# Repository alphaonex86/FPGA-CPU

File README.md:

# FPGA-CPU

An x86 CPU in an FPGA, on an interposer that plugs into an original PC CPU
socket and runs the board's stock BIOS, chipset, RAM and disks.

Planned brand name for the ASIC build: **LastUpgrade** — the last upgrade
for an old board: with its own memory (large L2, on-module RAM) and
SSE2, it should run a modern OS at correct performance.

Linked project: [FPGAmotherboard](https://github.com/alphaonex86/FPGAmotherboard),
the reverse (a real CPU on a board whose chipset is an FPGA) for the same
sockets; the socket KiCad models in `sockets/kicad/` come from it.

## Goals

- ISA: i686 + x87 + MMX + SSE + SSE2 first (modern software such as Node.js
  requires SSE2), then x86-64 and SSE3..SSE4.2 (x86-64-v2).
- Large on-chip L2 (>= 128 KB) to hide the slow front-side bus and board RAM.
- Best possible performance on each platform; many configurations (ISA level,
  cache sizes, clocks) from one RTL tree.
- Optional RAM on the module, next to the FPGA.
- Vendor-neutral RTL, so a popular model could later become an ASIC.

## Target boards

| Socket | Board | Chipset | Host bus |
|---|---|---|---|
| Socket 3 | Biostar MB-8433UUD | UMC 8881F / 8886BF | 486, 32-bit, 25/33/40 MHz |
| Socket 7 | Biostar MB-8500TTD | Intel 430TX | P5, 64-bit, 60/66 MHz |
| Socket 370 | VIA Apollo Pro 133A board (TBD) | VT82C694X | P6 AGTL+, 66/100/133 MHz |

## FPGAs

| FPGA | Logic | Block RAM | Package | Free toolchain |
|---|---|---|---|---|
| Altera Cyclone V E A9 — 5CEBA9/5CEFA9F23C8N (preferred) | 301k LE | 14.25 Mb | F484, 23x23 mm, 1.0 mm pitch, 224 I/O | Quartus Prime Lite (no licence) |
| Efinix Titanium Ti180 — TI180G400C3 | 176k LE | 13.1 Mb | 16x16 mm, 0.8 mm pitch, 274 I/O | Efinity (no licence) |

Both had authorized distributor stock at the end of 2026. The survey, I/O budget
per socket and power budget are in [FPGAlist/README.md](FPGAlist/README.md).

## Status

Planning: FPGAs chosen, documentation collected. No RTL yet.

## Layout

- `AGENTS.md` — project rules and requirements.
- `FPGAlist/` — FPGA survey; `CycloneV_A9/` and `Ti180_G400/` hold the vendor
  documentation, pin-outs, models, board references and toolchain notes.
- `sockets/` — per socket: CPU datasheets (bus protocol, pinout, power),
  chipset datasheets and the target board's manual, BIOS dump and photo;
  `kicad/` holds the socket footprints, symbols, 3D models and pin maps.
- `isa/` — x86 ISA manuals (Intel SDM, AMD APM, CPUID AP-485).
- `plan/` — interposer board plan (3 sockets x 2 FPGAs) and the prompt to run it.
- `fetch.sh` — downloads everything listed in the `sources.txt` files.

## Offline documentation

Vendor files are not stored in git (copyright, size). Download them with:

    ./fetch.sh FPGAlist/*/sources.txt sockets/sources.txt isa/sources.txt sockets/local-sources.txt

`sockets/local-sources.txt` copies files from the operator's local archive
(`file://`). No VT82C694X datasheet was found: use the VT82C694T one and
86Box's model (`FPGAcommon/86Box`).

Quartus and Efinity need a vendor account: see
[FPGAlist/CycloneV_A9/README.md](FPGAlist/CycloneV_A9/README.md) and
[FPGAlist/Ti180_G400/README.md](FPGAlist/Ti180_G400/README.md).

## License

GPL-3.0, see [LICENSE](LICENSE).

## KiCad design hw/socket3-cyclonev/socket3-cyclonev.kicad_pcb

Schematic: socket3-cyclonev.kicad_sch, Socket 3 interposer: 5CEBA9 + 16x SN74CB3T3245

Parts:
C1, C8, C12, C16: 10uF/25V; C_1210_3225Metric
C2: 4.7uF/25V; C_0805_2012Metric
C3, C4: 22uF/10V; C_1206_3216Metric
C5, C10, C14, C18, C21, C68, C69, C70, C90, C91, C92, C105, C106, C107, C108, C109, C110, C111, C112, C113, C114, C115, C116, C117, C118, C119, C120, C121: 100nF; C_0402_1005Metric
C6, C20, C44, C45, C46, C47, C48, C49, C50, C51: 10nF; C_0402_1005Metric
C7: 27nF; C_0402_1005Metric
C9, C13, C17: 22uF/6.3V; C_0805_2012Metric
C11, C15, C19: 3.3nF; C_0402_1005Metric
C22, C23, C24, C25, C26, C27, C28, C29, C30, C31, C32, C33, C34, C78, C79, C80, C81: 4.7nF; C_0402_P1.00
C35, C36, C37, C38, C39, C40, C41, C42, C43, C82, C83, C84, C85, C95: 10nF; C_0402_P1.00
C52, C53, C54, C55, C56, C57, C58, C59, C60, C61, C62, C63: 22nF; C_0402_1005Metric
C64, C65, C66, C67, C89: 47nF; C_0402_1005Metric
C71, C72: 220nF; C_0402_1005Metric
C73: 470nF; C_0402_1005Metric
C74, C93, C94: 1uF; C_0402_1005Metric
C75, C76, C77: 2.2nF; C_0402_P1.00
C86, C87: 22nF; C_0402_P1.00
C88: 47nF; C_0402_P1.00
C96, C98: 100nF; C_0402_P1.00
C97: 1uF; C_0402_P1.00
C99, C100, C101: 100uF/6.3V; C_1210_3225Metric
C102: 4.7uF; C_0603_1608Metric
C103: 10uF; C_0805_2012Metric
C104: 22uF; C_0805_2012Metric
F1: 2A; Fuse_1206_3216Metric
FB1: BLM18AG601SN1D; L_0603_1608Metric
J1: Conn_02x03_Odd_Even; PinHeader_2x03_P2.54mm_Vertical
J3: Barrel_Jack; BarrelJack_CUI_PJ-063AH_Horizontal
L1: 6.8uH FXL1040-6R8; L_Changjiang_FXL1040
L2, L3, L4: 2.2uH XFL4020-222; L_Coilcraft_XxL4020
PS1: TPS54620RHL; TI_RHL0014A
PS2, PS3, PS4: TPS62130RGT; VQFN-16-1EP_3x3mm_P0.5mm_EP1.68x1.68mm
R1, R2, R4: 4k7; R_0402_1005Metric
R3, R23, R26, R28, R29, R31, R33: 100k; R_0402_1005Metric
R5, R6, R7, R8, R9, R10, R11, R12, R13, R14, R15, R16, R17, R19, R20, R25, R36, R37: 10k; R_0402_1005Metric
R18: 1k; R_0402_1005Metric
R21: 2k0 1%; R_0402_1005Metric
R22: 1.33k; R_0402_1005Metric
R24: 52.3k; R_0402_1005Metric
R27: 37.4k; R_0402_1005Metric
R30: 215k; R_0402_1005Metric
R32: 316k; R_0402_1005Metric
R34: 68.1k 1%; R_0402_1005Metric
R35: 10k 1%; R_0402_1005Metric
TR01, TR02, TR03, TR04, TR05, TR06, TR07, TR08, TR09, TR10, TR11, TR12, TR13, TR14, TR15, TR16: SN74CB3T3245; TSSOP-20_4.4x6.5mm_P0.65mm
U1: FPGA_CycloneV_5CEFA9_F484; FPGA_CycloneV_5CEFA9_F484_BGA
U2: Socket3_Am5x86_PGA168; Socket3_Base_PGA168
U3: TLV6700DDC; SOT-23-6
U4: MT25QL01GBBB8ESF-0SIT; SOIC-16W_7.5x10.3mm_P1.27mm

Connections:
/A2: TR14.9 (A8), U1.N20
/A3: TR13.7 (A6), U1.N21
/A4: TR13.4 (A3), U1.W21
/A5: TR14.7 (A6), U1.W19
/A6: TR05.5 (A4), U1.Y21
/A7: TR14.8 (A7), U1.Y19
/A8: TR05.2 (A1), U1.AA22
/A9: TR14.6 (A5), U1.AB15
/A10: TR13.3 (A2), U1.Y20
/A11: TR13.6 (A5), U1.W22
/A12: TR06.2 (A1), U1.AB17
/A13: TR06.3 (A2), U1.AA18
/A14: TR14.5 (A4), U1.Y17
/A15: TR05.3 (A2), U1.Y22
/A16: TR06.4 (A3), U1.AA17
/A17: TR15.8 (A7), U1.Y15
/A18: TR05.4 (A3), U1.AB21
/A19: TR15.9 (A8), U1.AB11
/A20: TR06.5 (A4), U1.V20
/A20M#: TR11.3 (A2), U1.D13
/A21: TR06.8 (A7), U1.AB13
/A22: TR14.4 (A3), U1.AA15
/A23: TR14.3 (A2), U1.Y16
/A24: TR14.2 (A1), U1.AA14
/A25: TR05.6 (A5), U1.AB20
/A26: TR06.7 (A6), U1.V19
/A27: TR06.9 (A8), U1.AB12
/A28: TR05.8 (A7), U1.V21
/A29: TR15.4 (A3), U1.AA9
/A30: TR15.5 (A4), U1.AB8
/A31: TR15.6 (A5), U1.T19
/ADS#: TR13.5 (A4), U1.U22
/AHOLD: R5.1, TR01.4 (A3), U1.H21
/AS_DATA0: U1.AB4, U4.15 (DQ0)
/AS_DATA1: U1.AB3, U4.8 (DQ1)
/AS_DATA2: U1.AA5, U4.9 (DQ2)
/AS_DATA3: R17.1, U1.T4, U4.1 (DQ3)
/AS_DCLK: R16.1, U1.V3, U4.16 (C)
/AS_nCS: U1.R4, U4.7 (S#)
/BE0#: TR07.6 (A5), U1.AA10
/BE1#: TR07.8 (A7), U1.AB7
/BE2#: TR07.9 (A8), U1.AB6
/BE3#: TR11.6 (A5), U1.A7
/BLAST#: TR13.8 (A7), U1.M22
/BOFF#: TR03.9 (A8), U1.A10
/BRDY#: TR04.8 (A7), U1.K20
/BREQ: TR05.9 (A8), U1.AA19
/BS8#: TR03.7 (A6), U1.B10
/BS16#: TR02.9 (A8), U1.B17
/BUS_OE#: R36.1, TR01.19 (OE#), TR02.19 (OE#), TR03.19 (OE#), TR04.19 (OE#), TR05.19 (OE#), TR06.19 (OE#), TR07.19 (OE#), TR08.19 (OE#), TR09.19 (OE#), TR10.19 (OE#), TR11.19 (OE#), TR12.19 (OE#), TR13.19 (OE#), TR14.19 (OE#), TR15.19 (OE#), TR16.19 (OE#), U3.6 (OUTB)
/CACHE#: TR01.6 (A5), U1.B20
/CFG_CLKUSR: U1.T8
/CFG_CONF_DONE: R14.1, U1.K6
/CFG_CRC_ERROR: U1.T17
/CFG_CvP_CONFDONE: U1.R22
/CFG_DATA5: U1.U7
/CFG_DATA6: U1.R6
/CFG_DATA7: U1.U8
/CFG_DATA8: U1.R5
/CFG_DATA9: U1.W8
/CFG_DATA10: U1.P6
/CFG_DATA11: U1.W9
/CFG_DATA12: U1.N6
/CFG_DATA13: U1.U6
/CFG_DATA14: U1.T7
/CFG_DATA15: U1.V6
/CFG_DEV_CLRn: U1.P22
/CFG_DEV_OE: U1.R21
/CFG_INIT_DONE: U1.T18
/CFG_PR_DONE: U1.M6
/CFG_PR_ERROR: U1.M7
/CFG_PR_READY: U1.R7
/CFG_PR_REQUEST: U1.T20
/CFG_nCEO: U1.T22
/CFG_nCONFIG: R15.1, U1.A4
/CFG_nSTATUS: R13.1, U1.H5
/CLK: TR11.4 (A3), U1.H16
/CLKMUL: TR13.9 (A8), U1.AB22
/D0: TR15.3 (A2), U1.Y10
/D1: TR16.9 (A8), U1.AA7
/D2: TR16.8 (A7), U1.V13
/D3: TR12.5 (A4), U1.D6
/D4: TR08.2 (A1), U1.AB5
/D5: TR08.4 (A3), U1.M21
/D6: TR16.6 (A5), U1.V9
/D7: TR16.7 (A6), U1.V10
/D8: TR12.3 (A2), U1.B5
/D9: TR04.9 (A8), U1.B6
/D10: TR12.2 (A1), U1.D9
/D11: TR11.5 (A4), U1.A8
/D12: TR04.5 (A4), U1.E7
/D13: TR11.8 (A7), U1.B7
/D14: TR08.3 (A2), U1.Y9
/D15: TR04.7 (A6), U1.C6
/D16: TR16.5 (A4), U1.M20
/D17: TR03.2 (A1), U1.C8
/D18: TR03.5 (A4), U1.D12
/D19: TR09.9 (A8), U1.E19
/D20: TR03.6 (A5), U1.C11
/D21: TR09.7 (A6), U1.G21
/D22: TR03.8 (A7), U1.A9
/D23: TR02.2 (A1), U1.E14
/D24: TR02.5 (A4), U1.A13
/D25: TR09.5 (A4), U1.E21
/D26: TR10.9 (A8), U1.B12
/D27: TR11.2 (A1), U1.B11
/D28: TR10.7 (A6), U1.J19
/D29: TR10.3 (A2), U1.D17
/D30: TR10.6 (A5), U1.C15
/D31: TR01.5 (A4), U1.C20
/DP0: R9.1, TR15.2 (A1), U1.AA8
/DP1: R10.1, TR04.6 (A5), U1.D7
/DP2: R11.1, TR12.4 (A3), U1.E9
/DP3: R12.1, TR02.3 (A2), U1.A12
/D/C#: TR07.4 (A3), U1.AA12
/EADS#: TR01.9 (A8), U1.F22
/FERR#: TR02.6 (A5), U1.A14
/FLUSH#: TR02.7 (A6), U1.C16
/F_TCK: J1.1, R18.1, U1.V5
/F_TDI: J1.5, R20.1, U1.W5
/F_TDO: J1.6, U1.M5
/F_TMS: J1.3, R19.1, U1.P5
/GND: C1.2, C2.2, C3.2, C4.2, C6.2, C7.2, C8.2, C9.2, C10.2, C11.2, C12.2, C13.2, C14.2, C15.2, C16.2, C17.2, C18.2, C19.2, C20.2, C21.2, C22.2, C23.2, C24.2, C25.2, C26.2, C27.2, C28.2, C29.2, C30.2, C31.2, C32.2, C33.2, C34.2, C35.2, C36.2, C37.2, C38.2, C39.2, C40.2, C41.2, C42.2, C43.2, C44.2, C45.2, C46.2, C47.2, C48.2, C49.2, C50.2, C51.2, C52.2, C53.2, C54.2, C55.2, C56.2, C57.2, C58.2, C59.2, C60.2, C61.2, C62.2, C63.2, C64.2, C65.2, C66.2, C67.2, C68.2, C69.2, C70.2, C71.2, C72.2, C73.2, C74.2, C75.2, C76.2, C77.2, C78.2, C79.2, C80.2, C81.2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
/HITM#: TR09.8 (A7), U1.D19
/HLDA: TR06.6 (A5), U1.U21
/HOLD: R4.1, TR03.4 (A3), U1.C9
/IGNNE#: TR01.3 (A2), U1.J21
/INTR: TR09.6 (A5), U1.K22
/INV: TR02.8 (A7), U1.A15
/KEN#: TR11.7 (A6), U1.E12
/LOCK#: TR07.3 (A2), U1.Y14
/M/IO#: TR15.7 (A6), U1.AB10
/NC_A17: U1.A17
/NC_A18: U1.A18
/NC_A19: U1.A19
/NC_A20: U1.A20
/NC_A22: U1.A22
/NC_AA1: U1.AA1
/NC_AA2: U1.AA2
/NC_B3: U1.B3
/NC_B4: U1.B4
/NC_B22: U1.B22
/NC_C1: U1.C1
/NC_C2: U1.C2
/NC_C18: U1.C18
/NC_C19: U1.C19
/NC_D3: U1.D3
/NC_D4: U1.D4
/NC_D22: U1.D22
/NC_E1: U1.E1
/NC_E2: U1.E2
/NC_E10: U1.E10
/NC_E15: U1.E15
/NC_E16: U1.E16
/NC_E17: U1.E17
/NC_E20: U1.E20
/NC_E22: U1.E22
/NC_F7: U1.F7
/NC_F9: U1.F9
/NC_F10: U1.F10
/NC_F12: U1.F12
/NC_F13: U1.F13
/NC_F14: U1.F14
/NC_F15: U1.F15
/NC_F18: U1.F18
/NC_F19: U1.F19
/NC_F20: U1.F20
/NC_G1: U1.G1
/NC_G2: U1.G2
/NC_G6: U1.G6
/NC_G8: U1.G8
/NC_G10: U1.G10
/NC_G11: U1.G11
/NC_G12: U1.G12
/NC_G13: U1.G13
/NC_G15: U1.G15
/NC_G16: U1.G16
/NC_G17: U1.G17
/NC_G18: U1.G18
/NC_G20: U1.G20
/NC_H6: U1.H6
/NC_H8: U1.H8
/NC_H9: U1.H9
/NC_H10: U1.H10
/NC_H11: U1.H11
/NC_H13: U1.H13
/NC_H14: U1.H14
/NC_H15: U1.H15
/NC_H18: U1.H18
/NC_H20: U1.H20
/NC_J1: U1.J1
/NC_J2: U1.J2
/NC_J7: U1.J7
/NC_J8: U1.J8
/NC_J9: U1.J9
/NC_J11: U1.J11
/NC_J13: U1.J13
/NC_J17: U1.J17
/NC_J18: U1.J18
/NC_K7: U1.K7
/NC_K9: U1.K9
/NC_K16: U1.K16
/NC_K17: U1.K17
/NC_K19: U1.K19
/NC_L1: U1.L1
/NC_L2: U1.L2
/NC_L7: U1.L7
/NC_L8: U1.L8
/NC_L9: U1.L9
/NC_L17: U1.L17
/NC_L18: U1.L18
/NC_M8: U1.M8
/NC_M9: U1.M9
/NC_M16: U1.M16
/NC_M18: U1.M18
/NC_N1: U1.N1
/NC_N2: U1.N2
/NC_N8: U1.N8
/NC_N9: U1.N9
/NC_N16: U1.N16
/NC_N19: U1.N19
/NC_P7: U1.P7
/NC_P8: U1.P8
/NC_P9: U1.P9
/NC_P12: U1.P12
/NC_P14: U1.P14
/NC_P16: U1.P16
/NC_P17: U1.P17
/NC_P18: U1.P18
/NC_P19: U1.P19
/NC_PS1_10: PS1.10 (EN)
/NC_PS3_4: PS3.4 (PG)
/NC_PS4_4: PS4.4 (PG)
/NC_R1: U1.R1
/NC_R2: U1.R2
/NC_R9: U1.R9
/NC_R10: U1.R10
/NC_R11: U1.R11
/NC_R12: U1.R12
/NC_R14: U1.R14
/NC_R15: U1.R15
/NC_R16: U1.R16
/NC_R17: U1.R17
/NC_T9: U1.T9
/NC_T10: U1.T10
/NC_T12: U1.T12
/NC_T13: U1.T13
/NC_T14: U1.T14
/NC_T15: U1.T15
/NC_TR04_A1: TR04.2 (A1)
/NC_TR04_A2: TR04.3 (A2)
/NC_TR04_A3: TR04.4 (A3)
/NC_TR04_B1: TR04.18 (B1)
/NC_TR04_B2: TR04.17 (B2)
/NC_TR04_B3: TR04.16 (B3)
/NC_TR08_A4: TR08.5 (A4)
/NC_TR08_A5: TR08.6 (A5)
/NC_TR08_A6: TR08.7 (A6)
/NC_TR08_A7: TR08.8 (A7)
/NC_TR08_A8: TR08.9 (A8)
/NC_TR08_B4: TR08.15 (B4)
/NC_TR08_B5: TR08.14 (B5)
/NC_TR08_B6: TR08.13 (B6)
/NC_TR08_B7: TR08.12 (B7)
/NC_TR08_B8: TR08.11 (B8)
/NC_TR12_A5: TR12.6 (A5)
/NC_TR12_A6: TR12.7 (A6)
/NC_TR12_A7: TR12.8 (A7)
/NC_TR12_A8: TR12.9 (A8)
/NC_TR12_B5: TR12.14 (B5)
/NC_TR12_B6: TR12.13 (B6)
/NC_TR12_B7: TR12.12 (B7)
/NC_TR12_B8: TR12.11 (B8)
/NC_TR16_A1: TR16.2 (A1)
/NC_TR16_A2: TR16.3 (A2)
/NC_TR16_A3: TR16.4 (A3)
/NC_TR16_B1: TR16.18 (B1)
/NC_TR16_B2: TR16.17 (B2)
/NC_TR16_B3: TR16.16 (B3)
/NC_U1: U1.U1
/NC_U2: U1.U2
/NC_U2_A13: U2.A13 (InternalNC)
/NC_U2_C13: U2.C13 (InternalNC)
/NC_U2_J1: U2.J1 (InternalNC)
/NC_U4_4: U4.4 (DNU)
/NC_U4_5: U4.5 (DNU)
/NC_U4_6: U4.6 (DNU)
/NC_U4_11: U4.11 (DNU)
/NC_U4_12: U4.12 (DNU)
/NC_U4_13: U4.13 (DNU)
/NC_U4_14: U4.14 (DNU)
/NC_U10: U1.U10
/NC_U11: U1.U11
/NC_U12: U1.U12
/NC_U13: U1.U13
/NC_U15: U1.U15
/NC_U16: U1.U16
/NC_U17: U1.U17
/NC_V11: U1.V11
/NC_V14: U1.V14
/NC_V15: U1.V15
/NC_V16: U1.V16
/NC_V18: U1.V18
/NC_W1: U1.W1
/NC_W2: U1.W2
/NC_W16: U1.W16
/NC_Y3: U1.Y3
/NC_Y4: U1.Y4
/NC_Y6: U1.Y6
/NMI: TR01.7 (A6), U1.C21
/PCD: TR07.7 (A6), U1.Y11
/PCHK#: TR13.2 (A1), U1.AB18
/PG_1V1: PS2.4 (PG), PS3.13 (EN), PS4.13 (EN), R29.1
/PG_5V: PS1.14 (PWRGD), PS2.13 (EN), R26.1
/PLOCK#: TR05.7 (A6), U1.AA20
/PS1_BOOT: C5.1, PS1.13 (BOOT)
/PS1_COMP: PS1.8 (COMP), R22.1
/PS1_CZ: C7.1, R22.2
/PS1_FB: PS1.7 (VSENSE), R24.2, R25.1
/PS1_RT: PS1.1 (RT/CLK), R23.1
/PS1_SS: C6.1, PS1.9 (SS/TR)
/PS1_SW: C5.2, L1.1, PS1.11 (PH), PS1.12 (PH)
/PS2_FB: PS2.5 (FB), R27.2, R28.1
/PS2_SS: C11.1, PS2.9 (SS/TR)
/PS2_SW: L2.1, PS2.1 (SW), PS2.2 (SW), PS2.3 (SW)
/PS3_FB: PS3.5 (FB), R30.2, R31.1
/PS3_SS: C15.1, PS3.9 (SS/TR)
/PS3_SW: L3.1, PS3.1 (SW), PS3.2 (SW), PS3.3 (SW)
/PS4_FB: PS4.5 (FB), R32.2, R33.1
/PS4_SS: C19.1, PS4.9 (SS/TR)
/PS4_SW: L4.1, PS4.1 (SW), PS4.2 (SW), PS4.3 (SW)
/PWT: TR07.5 (A4), U1.U20
/RDY#: TR03.3 (A2), U1.L22
/RESET: TR10.2 (A1), U1.B16
/RREF_TL: R21.1, U1.A1
/SMI#: TR09.4 (A3), U1.D21
/SMIACT#: TR10.4 (A3), U1.B15
/SRESET: R6.1, TR02.4 (A3), U1.B13
/STPCLK#: TR11.9 (A8), U1.A5
/S_A2: TR14.11 (B8), U2.Q14 (A2)
/S_A3: TR13.13 (B6), U2.R15 (A3)
/S_A4: TR13.16 (B3), U2.S16 (A4)
/S_A5: TR14.13 (B6), U2.Q12 (A5)
/S_A6: TR05.15 (B4), U2.S15 (A6)
/S_A7: TR14.12 (B7), U2.Q13 (A7)
/S_A8: TR05.18 (B1), U2.R13 (A8)
/S_A9: TR14.14 (B5), U2.Q11 (A9)
/S_A10: TR13.17 (B2), U2.S13 (A10)
/S_A11: TR13.14 (B5), U2.R12 (A11)
/S_A12: TR06.18 (B1), U2.S7 (A12)
/S_A13: TR06.17 (B2), U2.Q10 (A13)
/S_A14: TR14.15 (B4), U2.S5 (A14)
/S_A15: TR05.17 (B2), U2.R7 (A15)
/S_A16: TR06.16 (B3), U2.Q9 (A16)
/S_A17: TR15.12 (B7), U2.Q3 (A17)
/S_A18: TR05.16 (B3), U2.R5 (A18)
/S_A19: TR15.11 (B8), U2.Q4 (A19)
/S_A20: TR06.15 (B4), U2.Q8 (A20)
/S_A20M#: TR11.17 (B2), U2.D15 (A20M)
/S_A21: TR06.12 (B7), U2.Q5 (A21)
/S_A22: TR14.16 (B3), U2.Q7 (A22)
/S_A23: TR14.17 (B2), U2.S3 (A23)
/S_A24: TR14.18 (B1), U2.Q6 (A24)
/S_A25: TR05.14 (B5), U2.R2 (A25)
/S_A26: TR06.13 (B6), U2.S2 (A26)
/S_A27: TR06.11 (B8), U2.S1 (A27)
/S_A28: TR05.12 (B7), U2.R1 (A28)
/S_A29: TR15.16 (B3), U2.P2 (A29)
/S_A30: TR15.15 (B4), U2.P3 (A30)
/S_A31: TR15.14 (B5), U2.Q1 (A31)
/S_ADS#: TR13.15 (B4), U2.S17 (ADS)
/S_AHOLD: TR01.16 (B3), U2.A17 (AHOLD)
/S_BE0#: TR07.14 (B5), U2.K15 (BE0)
/S_BE1#: TR07.12 (B7), U2.J16 (BE1)
/S_BE2#: TR07.11 (B8), U2.J15 (BE2)
/S_BE3#: TR11.14 (B5), U2.F17 (BE3)
/S_BLAST#: TR13.12 (B7), U2.R16 (BLAST)
/S_BOFF#: TR03.11 (B8), U2.D17 (BOFF)
/S_BRDY#: TR04.12 (B7), U2.H15 (BRDY)
/S_BREQ: R2.1, TR05.11 (B8), U2.Q15 (BREQ)
/S_BS8#: TR03.13 (B6), U2.D16 (BS8)
/S_BS16#: TR02.11 (B8), U2.C17 (BS16)
/S_CACHE#: TR01.14 (B5), U2.B12 (CACHE)
/S_CLK: TR11.16 (B3), U2.C3 (CLK)
/S_CLKMUL: TR13.11 (B8), U2.R17 (CLKMUL)
/S_D0: TR15.17 (B2), U2.P1 (D0)
/S_D1: TR16.11 (B8), U2.N2 (D1)
/S_D2: TR16.12 (B7), U2.N1 (D2)
/S_D3: TR12.15 (B4), U2.H2 (D3)
/S_D4: TR08.18 (B1), U2.M3 (D4)
/S_D5: TR08.16 (B3), U2.J2 (D5)
/S_D6: TR16.14 (B5), U2.L2 (D6)
/S_D7: TR16.13 (B6), U2.L3 (D7)
/S_D8: TR12.17 (B2), U2.F2 (D8)
/S_D9: TR04.11 (B8), U2.D1 (D9)
/S_D10: TR12.18 (B1), U2.E3 (D10)
/S_D11: TR11.15 (B4), U2.C1 (D11)
/S_D12: TR04.15 (B4), U2.G3 (D12)
/S_D13: TR11.12 (B7), U2.D2 (D13)
/S_D14: TR08.17 (B2), U2.K3 (D14)
/S_D15: TR04.13 (B6), U2.F3 (D15)
/S_D16: TR16.15 (B4), U2.J3 (D16)
/S_D17: TR03.18 (B1), U2.D3 (D17)
/S_D18: TR03.15 (B4), U2.C2 (D18)
/S_D19: TR09.11 (B8), U2.B1 (D19)
/S_D20: TR03.14 (B5), U2.A1 (D20)
/S_D21: TR09.13 (B6), U2.B2 (D21)
/S_D22: TR03.12 (B7), U2.A2 (D22)
/S_D23: TR02.18 (B1), U2.A4 (D23)
/S_D24: TR02.15 (B4), U2.A6 (D24)
/S_D25: TR09.15 (B4), U2.B6 (D25)
/S_D26: TR10.11 (B8), U2.C7 (D26)
/S_D27: TR11.18 (B1), U2.C6 (D27)
/S_D28: TR10.13 (B6), U2.C8 (D28)
/S_D29: TR10.17 (B2), U2.A8 (D29)
/S_D30: TR10.14 (B5), U2.C9 (D30)
/S_D31: TR01.15 (B4), U2.B8 (D31)
/S_DP0: TR15.18 (B1), U2.N3 (DP0)
/S_DP1: TR04.14 (B5), U2.F1 (DP1)
/S_DP2: TR12.16 (B3), U2.H3 (DP2)
/S_DP3: TR02.17 (B2), U2.A5 (DP3)
/S_D/C#: TR07.16 (B3), U2.M15 (D_C)
/S_EADS#: TR01.11 (B8), U2.B17 (EADS)
/S_FERR#: TR02.14 (B5), U2.C14 (FERR)
/S_FLUSH#: TR02.13 (B6), U2.C15 (FLUSH)
/S_HITM#: TR09.12 (B7), U2.A12 (HITM)
/S_HLDA: R1.1, TR06.14 (B5), U2.P15 (HLDA)
/S_HOLD: TR03.16 (B3), U2.E15 (HOLD)
/S_IGNNE#: TR01.17 (B2), U2.A15 (IGNNE)
/S_INTR: TR09.14 (B5), U2.A16 (INTR)
/S_INV: TR02.12 (B7), U2.A10 (INV)
/S_KEN#: TR11.13 (B6), U2.F15 (KEN)
/S_LOCK#: TR07.17 (B2), U2.N15 (LOCK)
/S_M/IO#: TR15.13 (B6), U2.N16 (M_IO)
/S_NMI: TR01.13 (B6), U2.B15 (NMI)
/S_PCD: TR07.13 (B6), U2.J17 (PCD)
/S_PCHK#: TR13.18 (B1), U2.Q17 (PCHK)
/S_PLOCK#: TR05.13 (B6), U2.Q16 (PLOCK)
/S_PWT: TR07.15 (B4), U2.L15 (PWT)
/S_RDY#: TR03.17 (B2), U2.F16 (RDY)
/S_RESET: R3.1, TR10.18 (B1), U2.C16 (RESET)
/S_SMI#: TR09.16 (B3), U2.B10 (SMI)
/S_SMIACT#: TR10.16 (B3), U2.C12 (SMIACT)
/S_SRESET: TR02.16 (B3), U2.C10 (SRESET)
/S_STPCLK#: TR11.11 (B8), U2.G15 (STPCLK)
/S_TCK: TR10.12 (B7), U2.A3 (TCK)
/S_TDI: TR01.18 (B1), U2.A14 (TDI)
/S_TDO: TR01.12 (B7), U2.B16 (TDO)
/S_TMS: TR09.18 (B1), U2.B14 (TMS)
/S_UP#: TR10.15 (B4), U2.C11 (UP)
/S_VCC: R34.1, U2.B7 (VCC), U2.B9 (VCC), U2.B11 (VCC), U2.C4 (VCC), U2.C5 (VCC), U2.E2 (VCC), U2.E16 (VCC), U2.G2 (VCC), U2.G16 (VCC), U2.H16 (VCC), U2.K2 (VCC), U2.K16 (VCC), U2.L16 (VCC), U2.M2 (VCC), U2.M16 (VCC), U2.P16 (VCC), U2.R3 (VCC), U2.R6 (VCC), U2.R8 (VCC), U2.R9 (VCC), U2.R10 (VCC), U2.R11 (VCC), U2.R14 (VCC)
/S_WB/WT#: TR09.17 (B2), U2.B13 (WB_WT)
/S_W/R#: TR07.18 (B1), U2.N17 (W_R)
/TCK: TR10.8 (A7), U1.C13
/TDI: TR01.2 (A1), U1.B18
/TDO: TR01.8 (A7), U1.J22
/TMS: TR09.2 (A1), U1.G22
/UP#: R8.1, TR10.5 (A4), U1.K21
/V3V3: C17.1, C75.1, C76.1, C77.1, C78.1, C79.1, C80.1, C81.1, C82.1, C83.1, C84.1, C85.1, C86.1, C87.1, C88.1, C89.1, C90.1, C91.1, C92.1, C93.1, C94.1, C103.1, C104.1, C105.1, C106.1, C107.1, C108.1, C109.1, C110.1, C111.1, C112.1, C113.1, C114.1, C115.1, C116.1, C117.1, C118.1, C119.1, C120.1, C121.1, L4.2, PS4.14 (VOS), R8.2, R9.2, R10.2, R11.2, R12.2, R13.2, R14.2, R15.2, R17.2, R19.2, R20.2, R32.1, R36.2, R37.2, TR01.20 (VCC), TR02.20 (VCC), TR03.20 (VCC), TR04.20 (VCC), TR05.20 (VCC), TR06.20 (VCC), TR07.20 (VCC), TR08.20 (VCC), TR09.20 (VCC), TR10.20 (VCC), TR11.20 (VCC), TR12.20 (VCC), TR13.20 (VCC), TR14.20 (VCC), TR15.20 (VCC), TR16.20 (VCC), U1.A6, U1.A16, U1.AA16, U1.AA21, U1.B19, U1.C7, U1.C10, U1.C12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
/V5: C3.1, C4.1, C8.1, C10.1, C12.1, C14.1, C16.1, C18.1, C21.1, L1.2, PS2.10 (AVIN), PS2.11 (PVIN), PS2.12 (PVIN), PS3.10 (AVIN), PS3.11 (PVIN), PS3.12 (PVIN), PS4.10 (AVIN), PS4.11 (PVIN), PS4.12 (PVIN), R24.1, R26.2, R29.2, U3.5 (VDD)
/V12: C1.1, C2.1, F1.2, PS1.4 (PVIN), PS1.5 (PVIN), PS1.6 (VIN)
/V12_IN: F1.1, J3.1
/VCCA_FPLL25: C98.1, FB1.2, U1.F4, U1.H19, U1.M3, U1.T3, U1.T5, U1.U18
/VCC_1V1: C9.1, C22.1, C23.1, C24.1, C25.1, C26.1, C27.1, C28.1, C29.1, C30.1, C31.1, C32.1, C33.1, C34.1, C35.1, C36.1, C37.1, C38.1, C39.1, C40.1, C41.1, C42.1, C43.1, C44.1, C45.1, C46.1, C47.1, C48.1, C49.1, C50.1, C51.1, C52.1, C53.1, C54.1, C55.1, C56.1, C57.1, C58.1, C59.1, C60.1, C61.1, C62.1, C63.1, C64.1, C65.1, C66.1, C67.1, C68.1, C69.1, C70.1, C71.1, C72.1, C73.1, C74.1, C99.1, C100.1, C101.1, C102.1, L2.2, PS2.14 (VOS), R27.1, U1.J4, U1.J10, U1.J12, U1.J14, U1.J16, U1.K3, U1.K5, U1.K11, U1.K13, U1.K15, U1.L4, U1.L10, U1.L12, U1.L14, U1.L16, U1.M11, U1.M13, U1.M15, U1.N4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
/VCC_AUX25: C13.1, C95.1, C96.1, C97.1, FB1.1, L3.2, PS3.14 (VOS), R30.1, U1.A3, U1.D11, U1.D18, U1.E6, U1.W7, U1.W13, U1.W18
/VCORE_OK: R37.1, U1.L19, U3.1 (OUTA)
/VCORE_SENSE: C20.1, R34.2, R35.1, U3.3 (INA+), U3.4 (INB-)
/WB/WT#: R7.1, TR09.3 (A2), U1.B21
/W/R#: TR07.2 (A1), U1.AA13

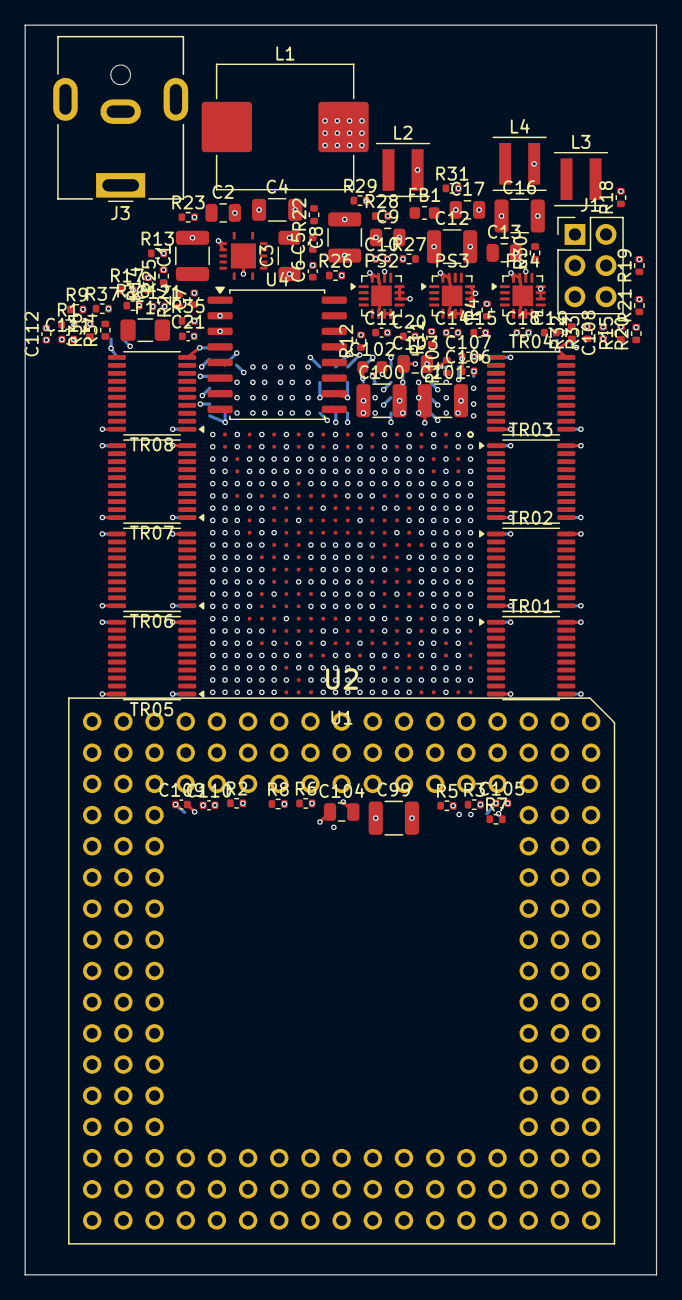
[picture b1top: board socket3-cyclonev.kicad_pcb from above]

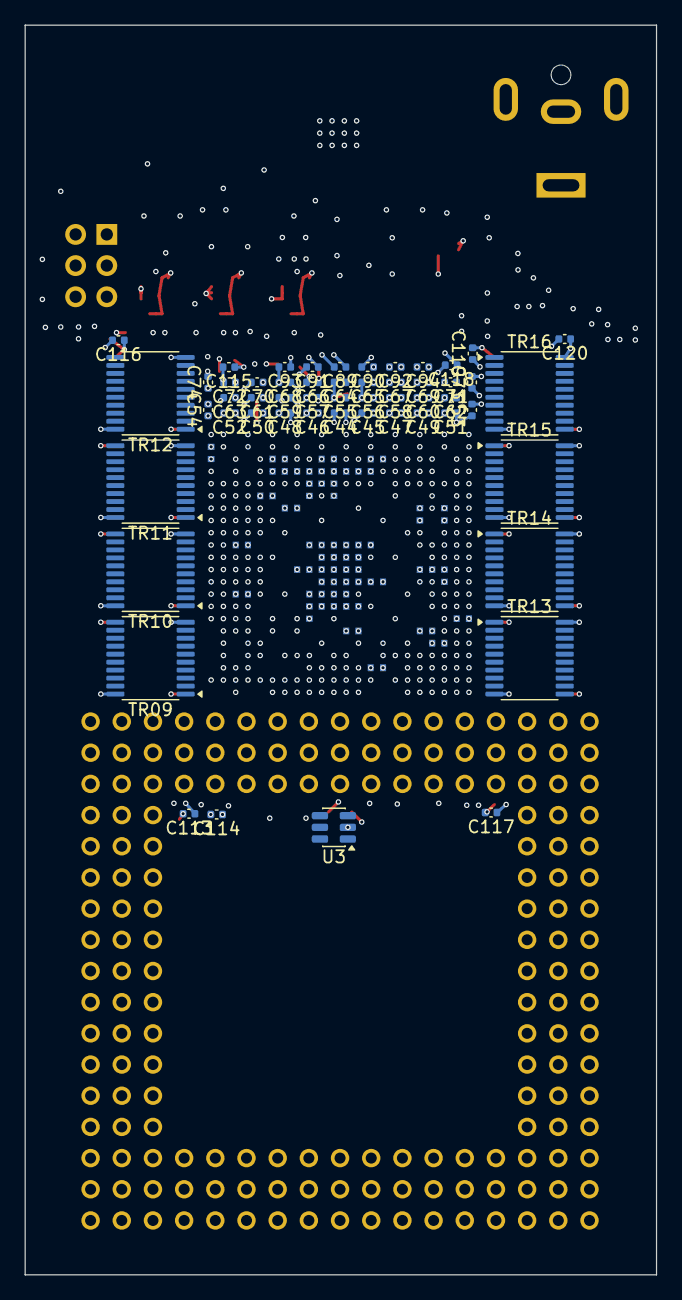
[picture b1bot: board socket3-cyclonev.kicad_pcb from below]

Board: 8 copper layers, 51.4 x 101.8 mm, 190 parts (94 on the bottom side), 270 nets.

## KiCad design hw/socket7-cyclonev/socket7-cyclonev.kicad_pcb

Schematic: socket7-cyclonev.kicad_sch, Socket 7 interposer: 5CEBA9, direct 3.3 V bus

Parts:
C1: 22uF/10V; C_0805_2012Metric
C2, C53, C54, C55, C75, C76, C77, C88: 100nF; C_0402_1005Metric
C3, C84: 22uF/6.3V; C_0805_2012Metric
C4: 1nF; C_0402_1005Metric
C5: 10uF/10V; C_0805_2012Metric
C6, C59, C78, C79: 1uF; C_0402_1005Metric
C7, C8, C9, C10, C11, C12, C13, C14, C15, C16, C17, C18, C19, C63, C64, C65, C66: 4.7nF; C_0402_P1.00
C20, C21, C22, C23, C24, C25, C26, C27, C28, C67, C68, C69, C70, C80: 10nF; C_0402_P1.00
C29, C30, C31, C32, C33, C34, C35, C36: 10nF; C_0402_1005Metric
C37, C38, C39, C40, C41, C42, C43, C44, C45, C46, C47, C48: 22nF; C_0402_1005Metric
C49, C50, C51, C52, C74: 47nF; C_0402_1005Metric
C56, C57: 220nF; C_0402_1005Metric
C58: 470nF; C_0402_1005Metric
C60, C61, C62: 2.2nF; C_0402_P1.00
C71, C72: 22nF; C_0402_P1.00
C73: 47nF; C_0402_P1.00
C81, C83: 100nF; C_0402_P1.00
C82: 1uF; C_0402_P1.00
C85: 10uF; C_0805_2012Metric
C86: 22uF; C_0805_2012Metric
C87: 4.7uF; C_0603_1608Metric
FB1: BLM18AG601SN1D; L_0603_1608Metric
J1: Conn_02x03_Odd_Even; PinHeader_2x03_P2.54mm_Vertical
L1: 1uH XFL4020-102; L_Coilcraft_XxL4020
PS1: TLV62585PDRL; SOT-563
PS2: TLV75725PDBVR; SOT-23-5
R1, R2, R3, R4, R5, R6, R7: 4k7; R_0402_1005Metric
R8, R9, R10, R11, R12, R14, R15: 10k; R_0402_1005Metric
R13: 1k; R_0402_1005Metric
R16: 2k0 1%; R_0402_1005Metric
R17: 82.5k; R_0402_1005Metric
R18, R19: 100k; R_0402_1005Metric
U1: FPGA_CycloneV_5CEFA9_F484; FPGA_CycloneV_5CEFA9_F484_BGA
U2: Intel_Pentium_MMX_P55C_Socket7; Socket7_Base_PGA296
U3: TPS22918DBVR; SOT-23-6
U4: MT25QL01GBBB8ESF-0SIT; SOIC-16W_7.5x10.3mm_P1.27mm

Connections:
/A3: U1.B7, U2.AL35 (A3)
/A4: U1.A7, U2.AM34 (A4)
/A5: U1.C9, U2.AK32 (A5)
/A6: U1.C11, U2.AN33 (A6)
/A7: U1.E12, U2.AL33 (A7)
/A8: U1.D12, U2.AM32 (A8)
/A9: U1.F14, U2.AK30 (A9)
/A10: U1.A10, U2.AN31 (A10)
/A11: U1.A8, U2.AL31 (A11)
/A12: U1.A9, U2.AL29 (A12)
/A13: U1.B10, U2.AK28 (A13)
/A14: U1.B11, U2.AL27 (A14)
/A15: U1.D13, U2.AK26 (A15)
/A16: U1.E14, U2.AL25 (A16)
/A17: U1.B12, U2.AK24 (A17)
/A18: U1.C13, U2.AL23 (A18)
/A19: U1.A12, U2.AK22 (A19)
/A20: U1.B13, U2.AL21 (A20)
/A20M#: U1.E16, U2.AK08 (A20M#)
/A21: U1.E9, U2.AF34 (A21)
/A22: U1.C6, U2.AH36 (A22)
/A23: U1.D6, U2.AE33 (A23)
/A24: U1.D7, U2.AG35 (A24)
/A25: U1.D9, U2.AJ35 (A25)
/A26: U1.B5, U2.AH34 (A26)
/A27: R7.1, U1.F12, U2.AG33 (A27)
/A28: U1.B6, U2.AK36 (A28)
/A29: U1.A5, U2.AK34 (A29)
/A30: U1.F13, U2.AM36 (A30)
/A31: U1.C8, U2.AJ33 (A31)
/ADS#: U1.C20, U2.AJ05 (ADS#)
/ADSC#: U1.C21, U2.AM02 (ADSC#)
/AHOLD: U1.K22, U2.V04 (AHOLD)
/AP: U1.D21, U2.AK02 (AP)
/APCHK#: U1.F22, U2.AE05 (APCHK#)
/AS_DATA0: U1.AB4, U4.15 (DQ0)
/AS_DATA1: U1.AB3, U4.8 (DQ1)
/AS_DATA2: U1.AA5, U4.9 (DQ2)
/AS_DATA3: R12.1, U1.T4, U4.1 (DQ3)
/AS_DCLK: R11.1, U1.V3, U4.16 (C)
/AS_nCS: U1.R4, U4.7 (S#)
/BE0#: U1.F15, U2.AL09 (BE0#)
/BE1#: U1.B17, U2.AK10 (BE1#)
/BE2#: U1.C16, U2.AL11 (BE2#)
/BE3#: U1.E15, U2.AK12 (BE3#)
/BE4#: U1.B16, U2.AL13 (BE4#)
/BE5#: U1.C15, U2.AK14 (BE5#)
/BE6#: U1.B15, U2.AL15 (BE6#)
/BE7#: U1.A15, U2.AK16 (BE7#)
/BOFF#: U1.J19, U2.Z04 (BOFF#)
/BP2: R5.1, U1.M22, U2.S03 (BP2)
/BP3: R6.1, U1.M21, U2.S05 (BP3)
/BRDY#: U1.K19, U2.X04 (BRDY#)
/BRDYC#: U1.J22, U2.Y03 (BRDYC#)
/BREQ: R1.1, U1.J17, U2.AJ01 (BREQ)
/BUSCHK#: U1.D17, U2.AL07 (BUSCHK#)
/CACHE#: U1.L22, U2.U03 (CACHE#)
/CFG_CLKUSR: U1.T8
/CFG_CONF_DONE: R9.1, U1.K6
/CFG_CRC_ERROR: U1.T17
/CFG_CvP_CONFDONE: U1.R22
/CFG_DATA5: U1.U7
/CFG_DATA6: U1.R6
/CFG_DATA7: U1.U8
/CFG_DATA8: U1.R5
/CFG_DATA9: U1.W8
/CFG_DATA10: U1.P6
/CFG_DATA11: U1.W9
/CFG_DATA12: U1.N6
/CFG_DATA13: U1.U6
/CFG_DATA14: U1.T7
/CFG_DATA15: U1.V6
/CFG_DEV_CLRn: U1.P22
/CFG_DEV_OE: U1.R21
/CFG_INIT_DONE: U1.T18
/CFG_PR_DONE: U1.M6
/CFG_PR_ERROR: U1.M7
/CFG_PR_READY: U1.R7
/CFG_PR_REQUEST: U1.T20
/CFG_nCEO: U1.T22
/CFG_nCONFIG: R10.1, U1.A4
/CFG_nSTATUS: R8.1, U1.H5
/CLK: U1.W16, U2.AK18 (CLK)
/CPUTYP: U1.L7, U2.Q35 (CPUTYP)
/D0: U1.T9, U2.K34 (D0)
/D1: U1.U10, U2.G35 (D1)
/D2: U1.T10, U2.J35 (D2)
/D3: U1.V9, U2.G33 (D3)
/D4: U1.T12, U2.F36 (D4)
/D5: U1.U11, U2.F34 (D5)
/D6: U1.T13, U2.E35 (D6)
/D7: U1.T14, U2.E33 (D7)
/D8: U1.AB5, U2.D34 (D8)
/D9: U1.U12, U2.C37 (D9)
/D10: U1.AA7, U2.C35 (D10)
/D11: U1.AB6, U2.B36 (D11)
/D12: U1.Y9, U2.D32 (D12)
/D13: U1.AA8, U2.B34 (D13)
/D14: U1.U13, U2.C33 (D14)
/D15: U1.AB7, U2.A35 (D15)
/D16: U1.AB8, U2.B32 (D16)
/D17: U1.AA9, U2.C31 (D17)
/D18: U1.T15, U2.A33 (D18)
/D19: U1.V13, U2.D28 (D19)
/D20: U1.AA10, U2.B30 (D20)
/D21: U1.Y11, U2.C29 (D21)
/D22: U1.AB10, U2.A31 (D22)
/D23: U1.AB11, U2.D26 (D23)
/D24: U1.U15, U2.C27 (D24)
/D25: U1.AA13, U2.C23 (D25)
/D26: U1.AB12, U2.D24 (D26)
/D27: U1.AB13, U2.C21 (D27)
/D28: U1.Y14, U2.D22 (D28)
/D29: U1.Y15, U2.C19 (D29)
/D30: U1.AA14, U2.D20 (D30)
/D31: U1.AB15, U2.C17 (D31)
/D32: U1.Y16, U2.C15 (D32)
/D33: U1.U16, U2.D16 (D33)
/D34: U1.AA17, U2.C13 (D34)
/D35: U1.AB17, U2.D14 (D35)
/D36: U1.AB18, U2.C11 (D36)
/D37: U1.Y17, U2.D12 (D37)
/D38: U1.AA19, U2.C09 (D38)
/D39: U1.AA18, U2.D10 (D39)
/D40: U1.U17, U2.D08 (D40)
/D41: U1.AA20, U2.A05 (D41)
/D42: U1.AB20, U2.E09 (D42)
/D43: U1.Y20, U2.B04 (D43)
/D44: U1.V18, U2.D06 (D44)
/D45: U1.W19, U2.C05 (D45)
/D46: U1.AB21, U2.E07 (D46)
/D47: U1.AA22, U2.C03 (D47)
/D48: U1.Y21, U2.D04 (D48)
/D49: U1.V19, U2.E05 (D49)
/D50: U1.R16, U2.D02 (D50)
/D51: U1.W21, U2.F04 (D51)
/D52: U1.Y22, U2.E03 (D52)
/D53: U1.V20, U2.G05 (D53)
/D54: U1.R17, U2.E01 (D54)
/D55: U1.V21, U2.G03 (D55)
/D56: U1.U20, U2.H04 (D56)
/D57: U1.U21, U2.J03 (D57)
/D58: U1.T19, U2.J05 (D58)
/D59: U1.P17, U2.K04 (D59)
/D60: U1.U22, U2.L05 (D60)
/D61: U1.P18, U2.L03 (D61)
/D62: U1.P19, U2.M04 (D62)
/D63: U1.N20, U2.N03 (D63)
/DP0: U1.V10, U2.D36 (DP0)
/DP1: U1.Y10, U2.D30 (DP1)
/DP2: U1.AA12, U2.C25 (DP2)
/DP3: U1.AA15, U2.D18 (DP3)
/DP4: U1.Y19, U2.C07 (DP4)
/DP5: U1.AB22, U2.F06 (DP5)
/DP6: U1.W22, U2.F02 (DP6)
/DP7: U1.N19, U2.N05 (DP7)
/D/C#: U1.B21, U2.AK04 (D/C#)
/EADS#: U1.D19, U2.AM04 (EADS#)
/EWBE#: U1.K21, U2.W03 (EWBE#)
/FERR#: U1.N21, U2.Q05 (FERR#)
/FLUSH#: U1.B18, U2.AN07 (FLUSH#)
/F_TCK: J1.1, R13.1, U1.V5
/F_TDI: J1.5, R15.1, U1.W5
/F_TDO: J1.6, U1.M5
/F_TMS: J1.3, R14.1, U1.P5
/GND: C1.2, C2.2, C3.2, C4.2, C5.2, C6.2, C7.2, C8.2, C9.2, C10.2, C11.2, C12.2, C13.2, C14.2, C15.2, C16.2, C17.2, C18.2, C19.2, C20.2, C21.2, C22.2, C23.2, C24.2, C25.2, C26.2, C27.2, C28.2, C29.2, C30.2, C31.2, C32.2, C33.2, C34.2, C35.2, C36.2, C37.2, C38.2, C39.2, C40.2, C41.2, C42.2, C43.2, C44.2, C45.2, C46.2, C47.2, C48.2, C49.2, C50.2, C51.2, C52.2, C53.2, C54.2, C55.2, C56.2, C57.2, C58.2, C59.2, C60.2, C61.2, C62.2, C63.2, C64.2, C65.2, C66.2, C67.2, C68.2, C69.2, C70.2, C71.2, C72.2, C73.2, C74.2, C75.2, C76.2, C77.2, C78.2, C79.2, C80.2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
/HIT#: U1.B20, U2.AK06 (HIT#)
/HITM#: U1.G16, U2.AL05 (HITM#)
/HLDA: U1.E21, U2.AJ03 (HLDA)
/HOLD: U1.G22, U2.AB04 (HOLD)
/IERR#: U1.M18, U2.P04 (IERR#)
/IGNNE#: U1.G8, U2.AA35 (IGNNE#)
/INIT: U1.G11, U2.AA33 (INIT)
/INTR/LINT0: U1.E7, U2.AD34 (INTR/LINT0)
/INV: U1.L19, U2.U05 (INV)
/KEN#: U1.K20, U2.W05 (KEN#)
/LOCK#: U1.G18, U2.AH04 (LOCK#)
/M/IO#: U1.L18, U2.T04 (M/IO#)
/NA#: U1.J21, U2.Y05 (NA#)
/NC_A17: U1.A17
/NC_A18: U1.A18
/NC_A19: U1.A19
/NC_A20: U1.A20
/NC_A22: U1.A22
/NC_AA1: U1.AA1
/NC_AA2: U1.AA2
/NC_B3: U1.B3
/NC_B4: U1.B4
/NC_B22: U1.B22
/NC_C1: U1.C1
/NC_C2: U1.C2
/NC_C18: U1.C18
/NC_C19: U1.C19
/NC_D3: U1.D3
/NC_D4: U1.D4
/NC_D22: U1.D22
/NC_E1: U1.E1
/NC_E2: U1.E2
/NC_E10: U1.E10
/NC_E17: U1.E17
/NC_E20: U1.E20
/NC_E22: U1.E22
/NC_F9: U1.F9
/NC_F10: U1.F10
/NC_F18: U1.F18
/NC_F19: U1.F19
/NC_F20: U1.F20
/NC_G1: U1.G1
/NC_G2: U1.G2
/NC_G10: U1.G10
/NC_G13: U1.G13
/NC_G20: U1.G20
/NC_H8: U1.H8
/NC_H9: U1.H9
/NC_H10: U1.H10
/NC_H11: U1.H11
/NC_H13: U1.H13
/NC_H14: U1.H14
/NC_H15: U1.H15
/NC_H16: U1.H16
/NC_H20: U1.H20
/NC_J1: U1.J1
/NC_J2: U1.J2
/NC_J8: U1.J8
/NC_J9: U1.J9
/NC_J11: U1.J11
/NC_J13: U1.J13
/NC_K9: U1.K9
/NC_K16: U1.K16
/NC_L1: U1.L1
/NC_L2: U1.L2
/NC_L9: U1.L9
/NC_M8: U1.M8
/NC_M9: U1.M9
/NC_M16: U1.M16
/NC_N1: U1.N1
/NC_N2: U1.N2
/NC_N9: U1.N9
/NC_N16: U1.N16
/NC_P9: U1.P9
/NC_P12: U1.P12
/NC_P14: U1.P14
/NC_P16: U1.P16
/NC_PS2_4: PS2.4 (NC)
/NC_R1: U1.R1
/NC_R2: U1.R2
/NC_R10: U1.R10
/NC_R11: U1.R11
/NC_R12: U1.R12
/NC_R14: U1.R14
/NC_R15: U1.R15
/NC_U1: U1.U1
/NC_U2: U1.U2
/NC_U4_4: U4.4 (DNU)
/NC_U4_5: U4.5 (DNU)
/NC_U4_6: U4.6 (DNU)
/NC_U4_11: U4.11 (DNU)
/NC_U4_12: U4.12 (DNU)
/NC_U4_13: U4.13 (DNU)
/NC_U4_14: U4.14 (DNU)
/NC_V11: U1.V11
/NC_V14: U1.V14
/NC_V15: U1.V15
/NC_V16: U1.V16
/NC_W1: U1.W1
/NC_W2: U1.W2
/NC_Y3: U1.Y3
/NC_Y4: U1.Y4
/NC_Y6: U1.Y6
/NMI/LINT1: U1.G12, U2.AC33 (NMI/LINT1)
/PCD: U1.H18, U2.AG05 (PCD)
/PCHK#: U1.K17, U2.AF04 (PCHK#)
/PEN#: U1.G6, U2.Z34 (PEN#)
/PG_1V1: PS1.6 (PG), PS2.3 (EN), R19.1, U3.3 (ON)
/PM0/BP0: R3.1, U1.L17, U2.Q03 (PM0/BP0)
/PM1/BP1: R4.1, U1.M20, U2.R04 (PM1/BP1)
/PRDY: U1.G21, U2.AC05 (PRDY)
/PS1_FB: PS1.5 (FB), R17.2, R18.1
/PS1_SW: L1.1, PS1.2 (SW)
/PWT: U1.E19, U2.AL03 (PWT)
/RESET: U1.A13, U2.AK20 (RESET)
/RREF_TL: R16.1, U1.A1
/SCYC: R2.1, U1.A14, U2.AL17 (SCYC)
/SMI#: U1.F7, U2.AB34 (SMI#)
/SMIACT#: U1.J18, U2.AG03 (SMIACT#)
/STPCLK#: U1.K7, U2.V34 (STPCLK#)
/S_VCC2: C1.1, C2.1, PS1.3 (VIN), PS1.4 (EN), U2.A07 (VCC2), U2.A09 (VCC2), U2.A11 (VCC2), U2.A13 (VCC2), U2.A15 (VCC2), U2.A17 (VCC2), U2.AA01 (VCC2), U2.AC01 (VCC2), U2.AE01 (VCC2), U2.AG01 (VCC2), U2.AN09 (VCC2), U2.AN11 (VCC2), U2.AN13 (VCC2), U2.AN15 (VCC2), U2.AN17 (VCC2), U2.AN19 (VCC2), U2.G01 (VCC2), U2.J01 (VCC2), U2.L01 (VCC2), U2.N01 (VCC2), U2.Q01 (VCC2), U2.S01 (VCC2), U2.U01 (VCC2), U2.W01 (VCC2), U2.Y01 (VCC2)
/S_VCC3: C5.1, C6.1, PS2.1 (IN), U2.A19 (VCC3), U2.A21 (VCC3), U2.A23 (VCC3), U2.A25 (VCC3), U2.A27 (VCC3), U2.A29 (VCC3), U2.AA37 (VCC3), U2.AC37 (VCC3), U2.AE37 (VCC3), U2.AG37 (VCC3), U2.AN21 (VCC3), U2.AN23 (VCC3), U2.AN25 (VCC3), U2.AN27 (VCC3), U2.AN29 (VCC3), U2.E37 (VCC3), U2.G37 (VCC3), U2.J37 (VCC3), U2.L33 (VCC3), U2.L37 (VCC3), U2.N37 (VCC3), U2.Q37 (VCC3), U2.S37 (VCC3), U2.T34 (VCC3), U2.U33 (VCC3), U2.U37 (VCC3), U2.W37 (VCC3), U2.Y37 (VCC3), U3.1 (VIN)
/TCK: U1.R9, U2.M34 (TCK)
/TDI: U1.P7, U2.N35 (TDI)
/TDO: U1.P8, U2.N33 (TDO)
/TMS: U1.N8, U2.P34 (TMS)
/TRST#: U1.L8, U2.Q33 (TRST#)
/U3_CT: C4.1, U3.4 (CT)
/VCC2DET#: U1.G17, U2.AL01 (VCC2DET#)
/VCCA_FPLL25: C83.1, FB1.2, U1.F4, U1.H19, U1.M3, U1.T3, U1.T5, U1.U18
/VCCIO33: C60.1, C61.1, C62.1, C63.1, C64.1, C65.1, C66.1, C67.1, C68.1, C69.1, C70.1, C71.1, C72.1, C73.1, C74.1, C75.1, C76.1, C77.1, C78.1, C79.1, C85.1, C86.1, C88.1, R8.2, R9.2, R10.2, R12.2, R14.2, R15.2, U1.A6, U1.A16, U1.AA16, U1.AA21, U1.B19, U1.C7, U1.C10, U1.C12, U1.C22, U1.D8, U1.D14, U1.D15, U1.D16, U1.E8, U1.E11, U1.E18, U1.F3, U1.F8, U1.F11, U1.F21, U1.G7, U1.G14, U1.H17, U1.J6, U1.K18, U1.L6, U1.M17, U1.M19, U1.N18, U1.P20, U1.P21, U1.R8, U1.R18, U1.R19, U1.T6, U1.T11, U1.U14, U1.U19, U1.V8, U1.W6, U1.W10, U1.W11, U1.W12, U1.W14, U1.W15, U1.W17, U1.W20, U1.Y8, U1.Y13, U3.5 (QOD), U3.6 (VOUT)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
/VCC_1V1: C3.1, C7.1, C8.1, C9.1, C10.1, C11.1, C12.1, C13.1, C14.1, C15.1, C16.1, C17.1, C18.1, C19.1, C20.1, C21.1, C22.1, C23.1, C24.1, C25.1, C26.1, C27.1, C28.1, C29.1, C30.1, C31.1, C32.1, C33.1, C34.1, C35.1, C36.1, C37.1, C38.1, C39.1, C40.1, C41.1, C42.1, C43.1, C44.1, C45.1, C46.1, C47.1, C48.1, C49.1, C50.1, C51.1, C52.1, C53.1, C54.1, C55.1, C56.1, C57.1, C58.1, C59.1, C84.1, L1.2, R17.1, R19.2, U1.J4, U1.J10, U1.J12, U1.J14, U1.J16, U1.K3, U1.K5, U1.K11, U1.K13, U1.K15, U1.L4, U1.L10, U1.L12, U1.L14, U1.L16, U1.M11, U1.M13, U1.M15, U1.N4, U1.N10, U1.N12, U1.N14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
/VCC_AUX25: C80.1, C81.1, C82.1, C87.1, FB1.1, PS2.5 (OUT), U1.A3, U1.D11, U1.D18, U1.E6, U1.W7, U1.W13, U1.W18
/WB/WT#: U1.H21, U2.AA05 (WB/WT#)
/W/R#: U1.G15, U2.AM06 (W/R#)
/[BF0]: U1.H6, U2.Y33 ([BF0])
/[BF1]: U1.J7, U2.X34 ([BF1])

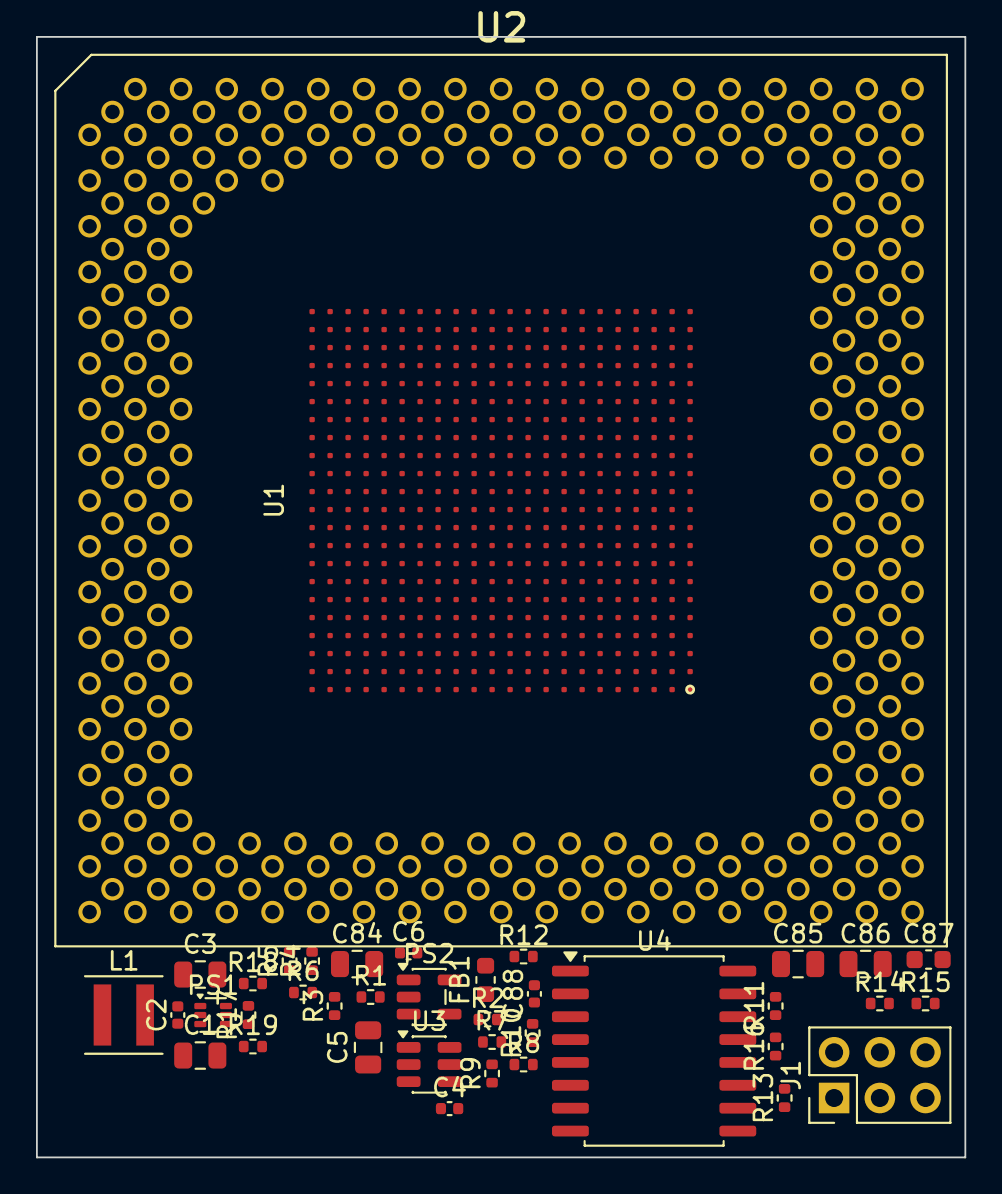
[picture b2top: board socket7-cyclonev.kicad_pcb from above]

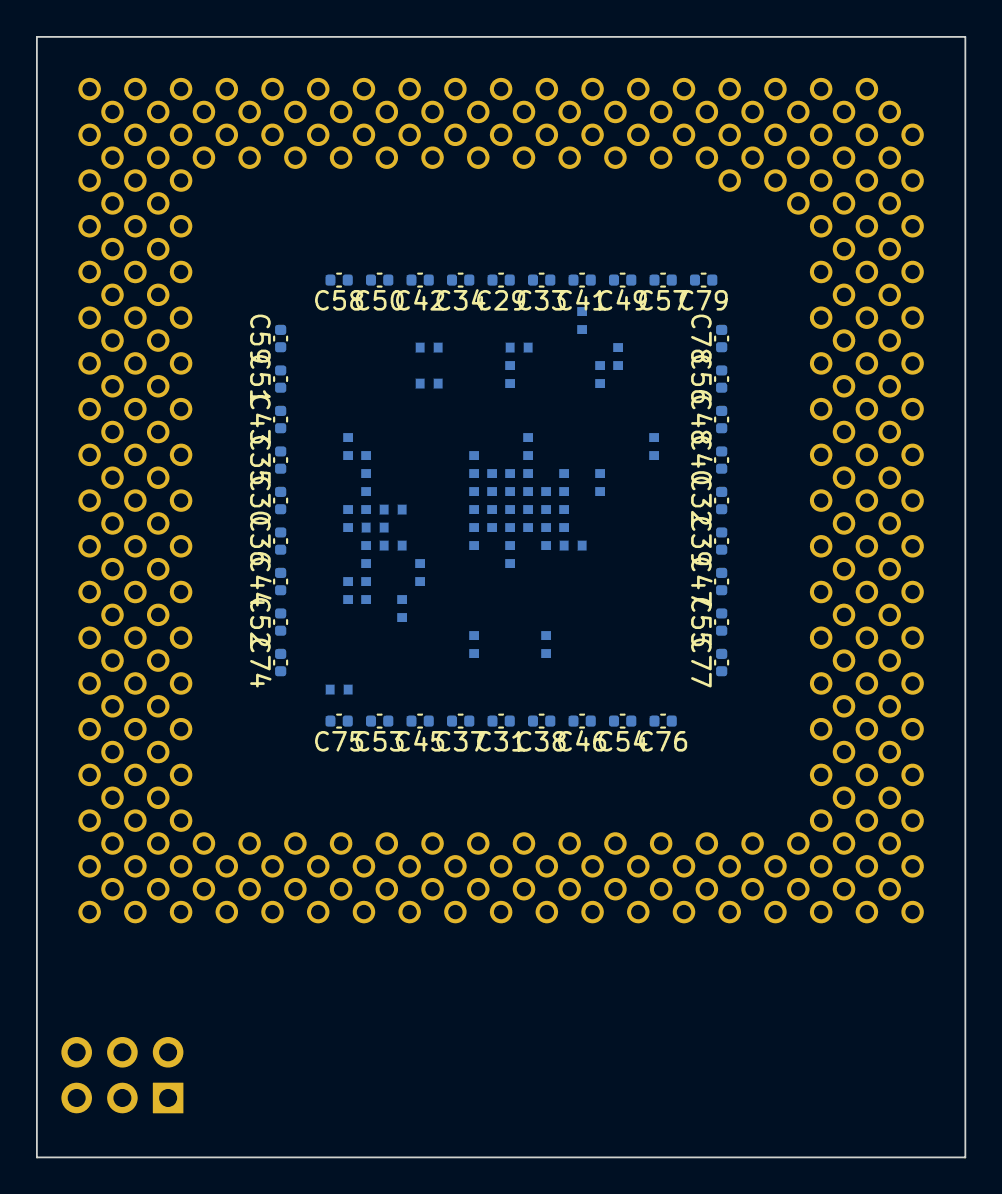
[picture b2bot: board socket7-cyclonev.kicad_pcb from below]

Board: 8 copper layers, 51.6 x 62.3 mm, 116 parts (77 on the bottom side), 191 nets, no tracks yet.
